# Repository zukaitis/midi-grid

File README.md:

# midi-grid
DIY RGB MIDI grid controller

midi-grid is an open source MIDI controller, main part of which is 8x8 LED illuminated button grid.

Main features of the device:
- 8x8 RGB LED illuminated button matrix
- 17 additional MIDI control buttons, most of them paired with RGB LED indicator
- 1 internal menu button
- 2 rotary encoders, acting as MIDI controls
- Monochrome LCD display with adjustable backlight
- Physical MIDI input and output ports

Currently device is developed to work with [Ableton Live](https://www.ableton.com/en/live/),
specifically with modified [Launchpad95](http://motscousus.com/stuff/2011-07_Novation_Launchpad_Ableton_Live_Scripts/)
MIDI remote script - [Launchpad95g](https://github.com/zukaitis/Launchpad95g). Additional functionality, like stand-alone modes,
or compatibility with other DAWs may be implemented later.

More thorough information, regarding design and implementation, is available in [wiki of this project](https://github.com/zukaitis/midi-grid/wiki).

**This repository uses submodules -** [here's info how to fully clone it](https://stackoverflow.com/questions/3796927/how-to-git-clone-including-submodules)

## Thanks to
- [@mimuz](https://github.com/mimuz) - for sharing [STM32 USB MIDI library](https://github.com/mimuz/mimuz-tuch)
- [@pidcodes](https://github.com/pidcodes) - for providing USB VID/PID pair for this application
- [@hdavid](https://github.com/hdavid) - for making an amazing Ableton Live extension - [Launchpad95](https://github.com/hdavid/Launchpad95)
- [@michaelbecker](https://github.com/michaelbecker) - for making [FreeRTOS C++ wrappers](https://michaelbecker.github.io/freertos-addons)

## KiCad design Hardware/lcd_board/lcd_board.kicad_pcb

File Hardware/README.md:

# Bill of Materials

| Reference | Quantity | Part number | Description | Catalog link
| --- | --- | --- | --- | ---
| A1 | 1 | Nokia 5110 LCD | LCD module, ILI9341 controller, TFT LCD Display, 9-pin breakout PCB, SPI interface, 5V/3.3V | https://www.ebay.com/itm/84-48-LCD-Module-White-Backlight-Adapter-PCB-for-Nokia-5110-Arduino/400488314619
| C3, C2, C1, C6, C7, C8, C9, C11, C13, C17 | 10 |  | Capacitor MLCC, 100nF +/-10%, 6.3V, 0603, X5R | 
| C12, C10, C4, C5 | 4 |  | Capacitor MLCC, 2.2uF +/-10%, 6.3V, 0603, X5R | 
| C14, C15 | 2 |  | Capacitor MLCC, 27pF +/-10%, 6.3V, 0603, C0G | 
| C16, C18, C19, C21, C20 | 5 |  | Capacitor MLCC, 10uF +/-10%, 6.3V, 1206, X5R | 
| D1, D3, D5, D7, D9, D11, D13, D15, D17, D19, D21, D23, D25, D27, D29, D31, D33, D35, D37, D39, D41, D43, D45, D47, D49, D51, D53, D55, D57, D59, D61, D63, D65, D67, D69, D71, D73, D75, D77, D79, D81, D83, D85, D87, D89, D91, D93, D95, D97, D99, D101, D103, D105, D107, D109, D111, D113, D115, D117, D119, D121, D123, D125, D127, D129, D132, D136, D140, D142, D148, D150, D156, D134, D144, D152, D146, D154 | 77 |  | RGB LED, TH, d=5mm, p=1.27mm, common anode, diffused, pinout: RAGB | https://www.ebay.com/itm/100pcs-x-5mm-RGB-LED-Common-Cathode-Tri-Color-Emitting-Diodes-Diffused/291498456335
| D2, D4, D6, D8, D10, D12, D14, D16, D18, D20, D22, D24, D26, D28, D30, D32, D34, D36, D38, D40, D42, D44, D46, D48, D50, D52, D54, D56, D58, D60, D62, D64, D66, D68, D70, D72, D74, D76, D78, D80, D82, D84, D86, D88, D90, D92, D94, D96, D98, D100, D102, D104, D106, D108, D110, D112, D114, D116, D118, D120, D122, D124, D126, D128, D130, D133, D137, D141, D143, D149, D151, D157, D131, D135, D138, D139, D145, D153, D147, D155, D158 | 81 | LL4148-GS08 | 100V 0.3A standard switching diode, MiniMELF | https://www.tme.eu/en/details/ll4148-gs08/smd-universal-diodes/vishay/
| F1 | 1 | 1206L050YR | Polyfuse, 6V, 500mA, 1206 | https://eu.mouser.com/productdetail/?qs=PWhpLWeW8wckT8hV5jLiAA%3D%3D
| J1 | 1 | 105017-0001 | Connector, Micro USB | https://www.lemona.lt/?page=item&i_id=216110
| J2, J3 | 2 | FC68133 | 3-pin audio jack receptable (stereo/TRS connector) with 2 switching contacts | http://lt.farnell.com/cliff-electronic-components/fc68133/stereo-jack-3-5mm-5pos-pcb/dp/2518190
| J4 | 1 | 22-27-2041 | Generic connector, single row, 01x04 | 
| Q2, Q1, Q4, Q3, Q6, Q5, Q8, Q7, Q10, Q9, Q12, Q11, Q14, Q13, Q16, Q15, Q18, Q17, Q20, Q19 | 20 | BSH205G2 | MOSFET, P Channel, -2 A, -20 V, SOT-23 | http://uk.farnell.com/nexperia/bsh205g2/mosfet-p-ch-20v-2a-to236ab/dp/2498570
| Q28, Q27, Q26, Q25, Q32, Q31, Q30, Q29, Q24, Q23, Q22, Q21, Q33, Q34 | 14 | NX7002AK | MOSFET, N-Channel, 190 mA, 60 V, SOT-23 | http://uk.farnell.com/nexperia/nx7002ak/mosfet-single-n-ch-60v-0-19a-sot23/dp/2191746
| R21, R22, R23, R24, R64 | 5 |  | Resistor, 1K +/-5%, 0603 | 
| R28, R27, R26, R25 | 4 |  | Resistor, 249R +/-1%, 1206 | 
| R36, R35, R34, R33 | 4 |  | Resistor, 294R +/-1%, 1206 | 
| R44, R43, R42, R41 | 4 |  | Resistor, 51R +/-1%, 1206 | 
| R40, R39, R38, R37, R48, R47, R46, R45, R32, R31, R30, R29, R1, R2, R3, R4, R5, R6, R7, R8, R9, R10, R11, R12, R13, R14, R15, R16, R17, R18, R19, R20, R52, R51, R50, R49, R53, R54, R55, R59, R56, R63 | 42 |  | Resistor, 10K +/-5% 0603 | 
| R57, R58, R61, R60, R62 | 5 |  | Resistor, 220R +/-5%, 0603 | 
| R65 | 1 |  | Resistor, 1.6K +/-5%, 0603 | 
| SW1, SW2, SW3, SW4 | 4 |  | 4 x 4 silicone push button matrix, button size: 15mm x 15mm, matrix size 100mm x 100mm | http://www.better-silicone.com/Translucent-Silicone-Rubber-Button-Pad-4x4-Keyboard-pd847135.html
| SW5, SW6, SW7, SW8, SW9, SW10, SW11, SW12, SW13, SW14, SW15, SW16, SW17, SW18, SW19, SW20, SW23, SW24 | 18 |  | Tactile switch with stem for cap, 12mm x 12mm, h=7.3mm | https://www.ebay.com/itm/25PCS-12x12x7-3mm-Tact-Tactile-Push-Button-Momentary-SMD-PCB-Switch-with-Cap/382202288162
|  | 17 |  | Button cap, round, d=12mm, black | 
|  | 1 |  | Button cap, round, d=12mm, red | 
| SW21, SW22 | 2 |  | Tactile switch, 6mm x 6mm, h=4.3mm | 
| SW25, SW26 | 2 | EC12E24204A9 | Rotary encoder, incremental, 24 pulses/revolution | 
| U1 | 1 | STM32F413RHT6 | Microcontroller, ARM Cortex-M4, LQFP64, Flash: 1536KB Ram: 320KB,100MHz Voltage: 1.7..3.6V IO-pins: 50 | 
| U4, U3, U2 | 3 | SN74HC138PW | Decoder 3 to 8 (active low outputs), TSSOP-16 | http://uk.farnell.com/texas-instruments/sn74hc138pw/ic-decoder-demux-smd/dp/9591095
| U5 | 1 | USBUF02W6 | 2-line EMI filter and ESD protection with R pull-up, for USB interfaces, SOT-363 | http://uk.farnell.com/stmicroelectronics/usbuf02w6/filter-low-pass-1ghz-sot-323-6/dp/2341659
| U6 | 1 | VO617A | Optocoupler, SO-4 | https://eu.mouser.com/ProductDetail/Vishay-Semiconductors/VO617A-8X017T?qs=%2fha2pyFaduga7JDI9Y4HlZSPCPCm8mReb3LRegGLigzOqtsvsZdCeQ%3d%3d
| U7 | 1 | LD1117STR | 800mA Low-Dropout Linear Regulator, adjustable output, SOT-223 | http://uk.farnell.com/stmicroelectronics/ld1117str/ic-v-reg-adj-1-25-15v-smd-1117/dp/1202824
| Y1 | 1 | ABM3B-8.000MHZ-B2-T | Crystal 8.0MHz 18pf 20ppm -20C +70C | https://eu.mouser.com/ProductDetail/?qs=NE97hfUNX0Ef9OqIOqO2cA%3D%3D
|  | 71 |  | Standoff, M2 * 5mm | https://www.ebay.com/itm/KNURLED-BRASS-SPACER-FEMALE-FEMALE-SCREW-PC-MOTHERBOARD-STANDOFF-M2-X-3MM-25MM-/122039617381
|  | 64 |  | Phillips screw, round head, M2 * 6mm | https://www.ebay.com/itm/M2-A2-304-Stainless-Steel-Phillips-Round-Head-Pan-Head-Screws-Bolts-M2-3-M2-60-/122691038427
|  | 23 |  | Phillips screw, flat head, M2 * 5mm | https://www.ebay.com/itm/M2-A2-304-Stainless-Steel-Phillips-Flat-Head-Screws-Bolts-M2-3mm-M2-60mm-/122689688965

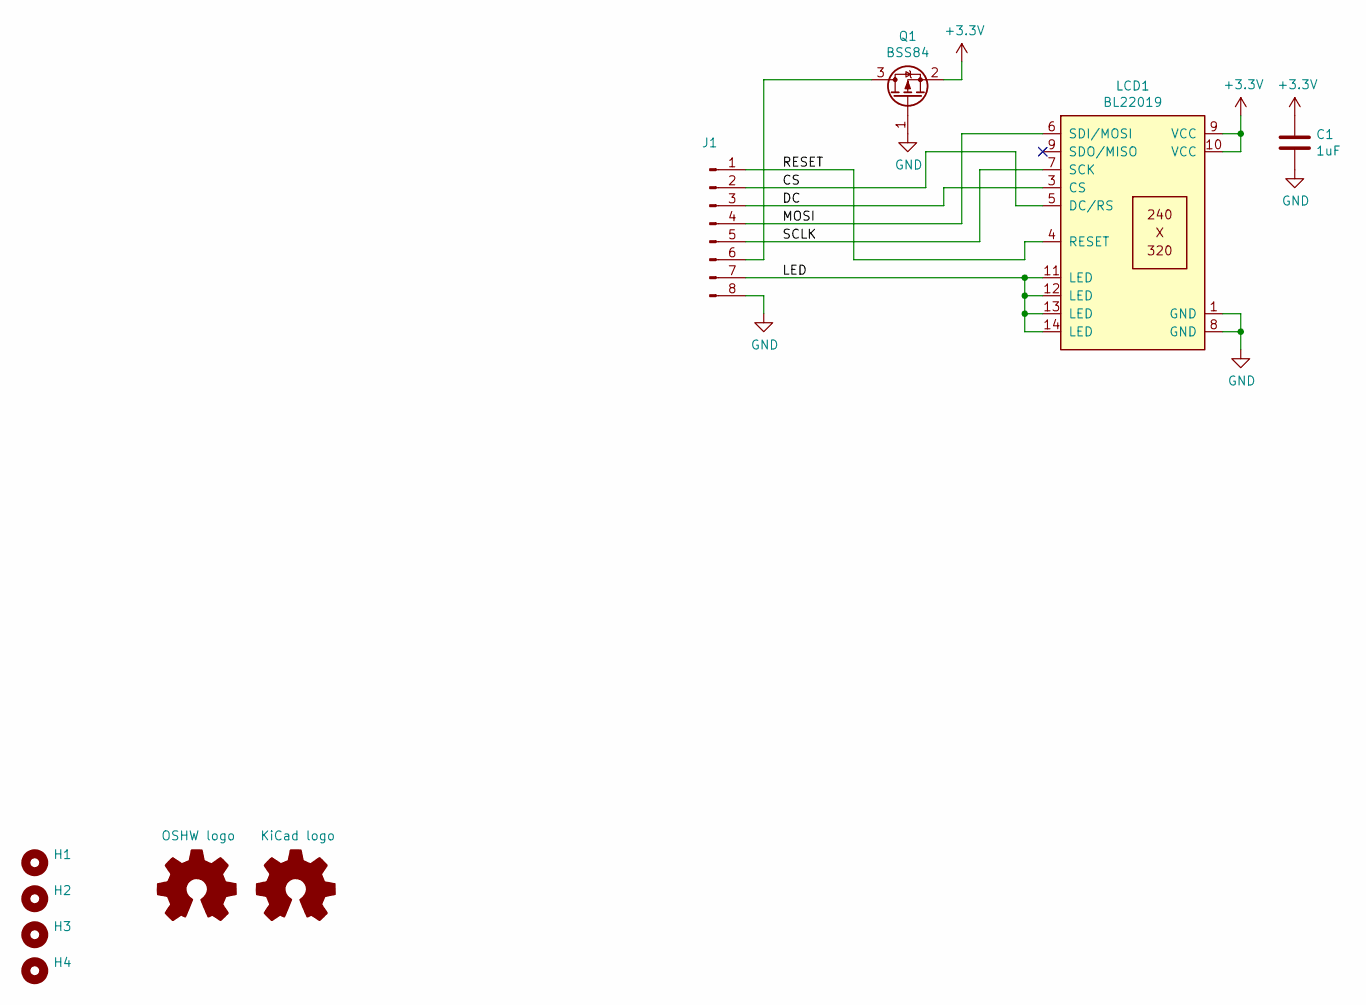
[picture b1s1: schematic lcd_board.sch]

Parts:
C1: 1uF; C_0805_2012Metric
H1, H2, H3, H4: MountingHole; MountingHole_2.2mm_M2
J1: Conn_01x08_Male; PinHeader_1x08_P2.54mm_Vertical_SMD_Pin1Left
LCD1: BL22019
LOGO1: OSHW logo; OSHW-Logo_11.4x12mm_Copper
LOGO2: KiCad logo; KiCad-Logo2_6mm_Copper
Q1: BSS84; SOT-23

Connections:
+3V3: C1.1, LCD1.9 (SDO/MISO), LCD1.10 (VCC), Q1.2 (S)
/CS: J1.2, LCD1.5 (DC/RS)
/DC: J1.3, LCD1.3 (CS)
/LED: J1.7, LCD1.11 (LED), LCD1.12 (LED), LCD1.13 (LED), LCD1.14 (LED)
/MOSI: J1.4, LCD1.6 (SDI/MOSI)
/RESET: J1.1, LCD1.4 (RESET)
/SCLK: J1.5, LCD1.7 (SCK)
GND: C1.2, J1.8, LCD1.1 (GND), LCD1.8 (GND), Q1.1 (G)
unnamed: J1.6, Q1.3 (D)

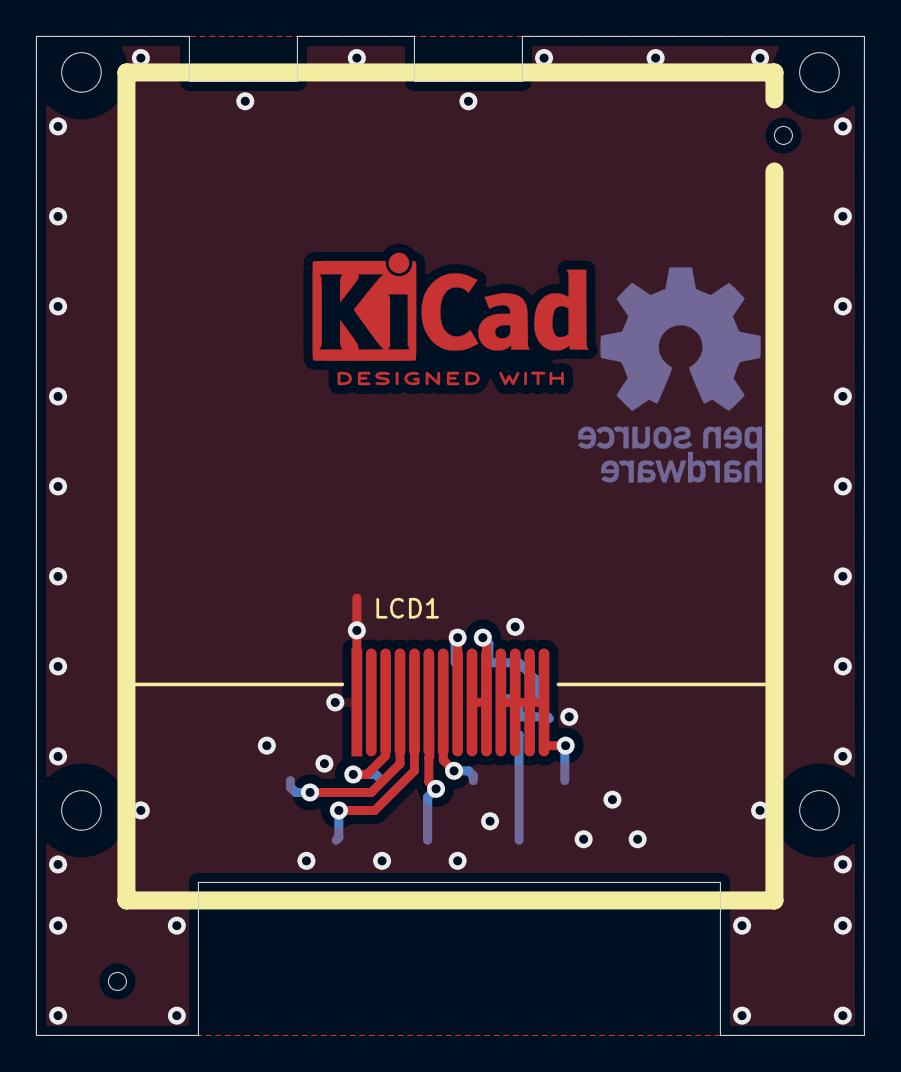
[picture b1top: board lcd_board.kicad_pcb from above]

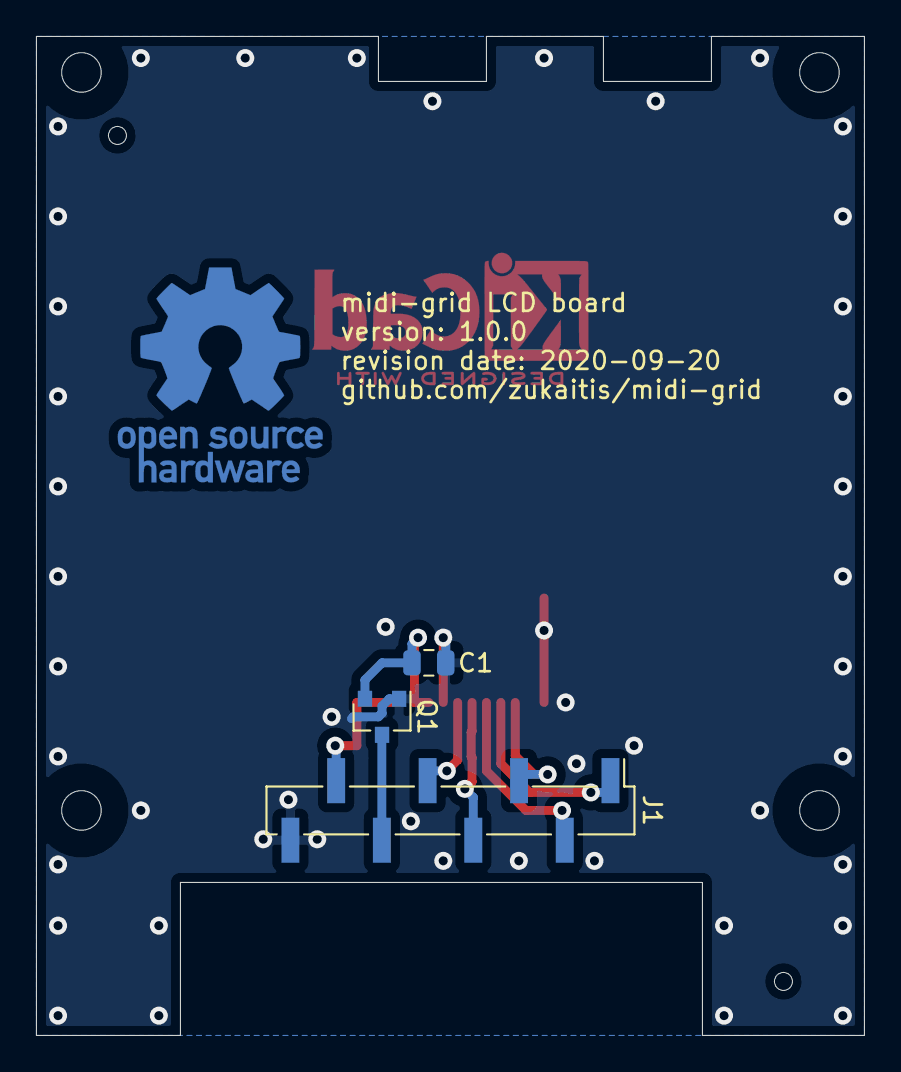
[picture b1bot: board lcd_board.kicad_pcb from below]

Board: 2 copper layers, 46.0 x 55.5 mm, 10 parts (4 on the bottom side), 9 nets.

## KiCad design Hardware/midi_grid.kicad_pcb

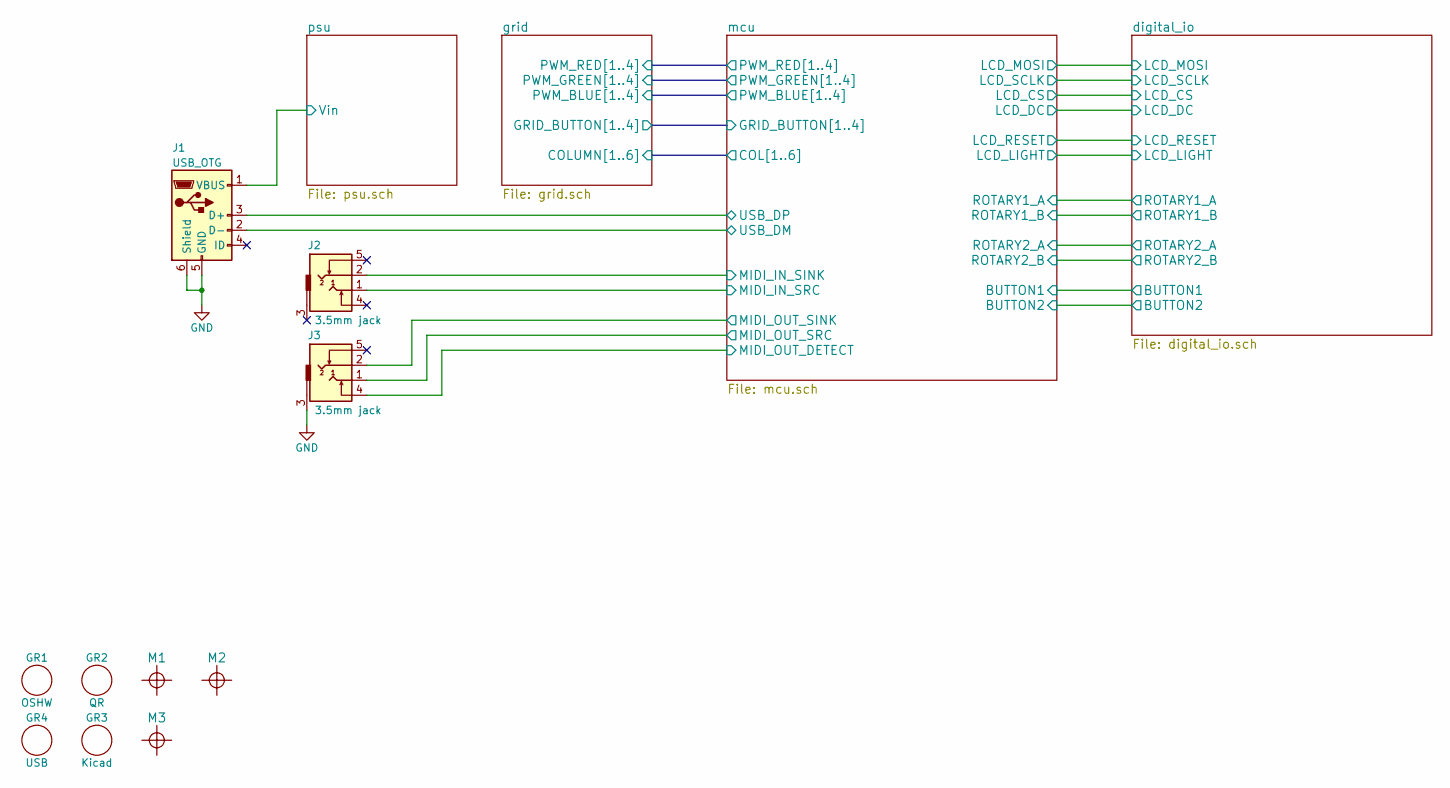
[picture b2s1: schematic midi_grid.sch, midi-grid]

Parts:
GR1: OSHW; Logo_OSHW
GR2: QR; qr_url
GR3: Kicad; Symbol_KiCAD-Logo_CopperAndSilkScreenTop
GR4: USB; usb_logo_6x3mm
J1: USB_OTG; USB_Micro-B_Molex-105017-0001
J2, J3: 3.5mm jack; 3.5mm-jack
M1, M2, M3: Mounting_hole; MountingHole_2.2mm_M2

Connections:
/mcu/MIDI_IN_SINK: J2.2; also elsewhere on the board
/mcu/MIDI_IN_SRC: J2.1; also elsewhere on the board
/mcu/MIDI_OUT_DETECT: J3.4; also elsewhere on the board
/mcu/MIDI_OUT_SINK: J3.2; also elsewhere on the board
/mcu/MIDI_OUT_SRC: J3.1; also elsewhere on the board
/mcu/USB_DM: J1.2 (D-); also elsewhere on the board
/mcu/USB_DP: J1.3 (D+); also elsewhere on the board
/psu/Vin: J1.1 (VBUS); also elsewhere on the board
GND: J1.5 (GND), J1.6 (Shield), J3.3; also elsewhere on the board

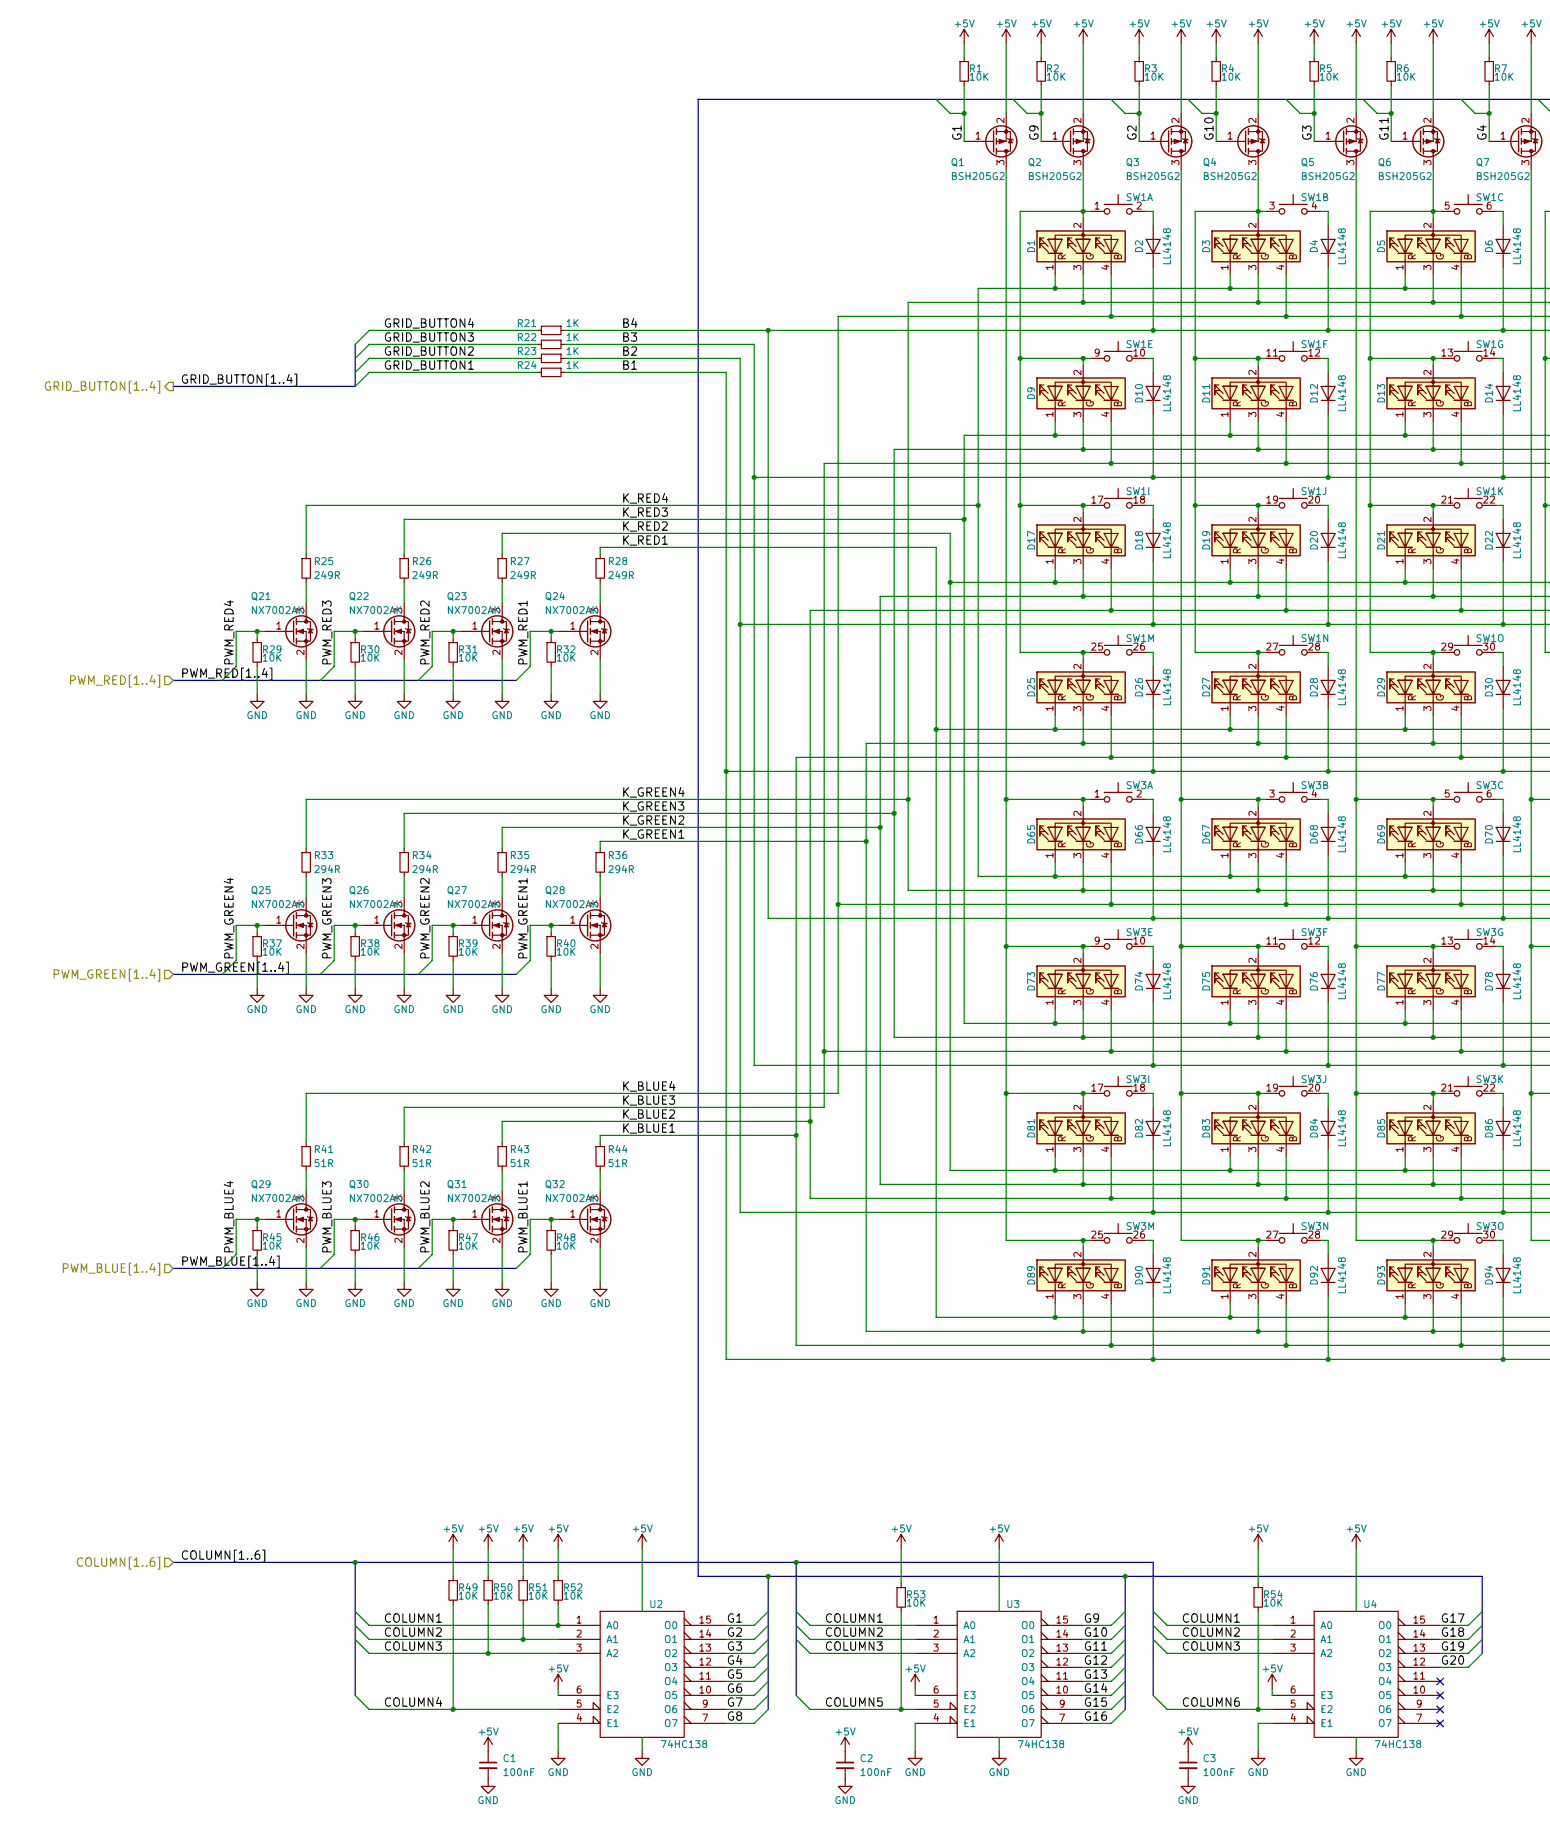
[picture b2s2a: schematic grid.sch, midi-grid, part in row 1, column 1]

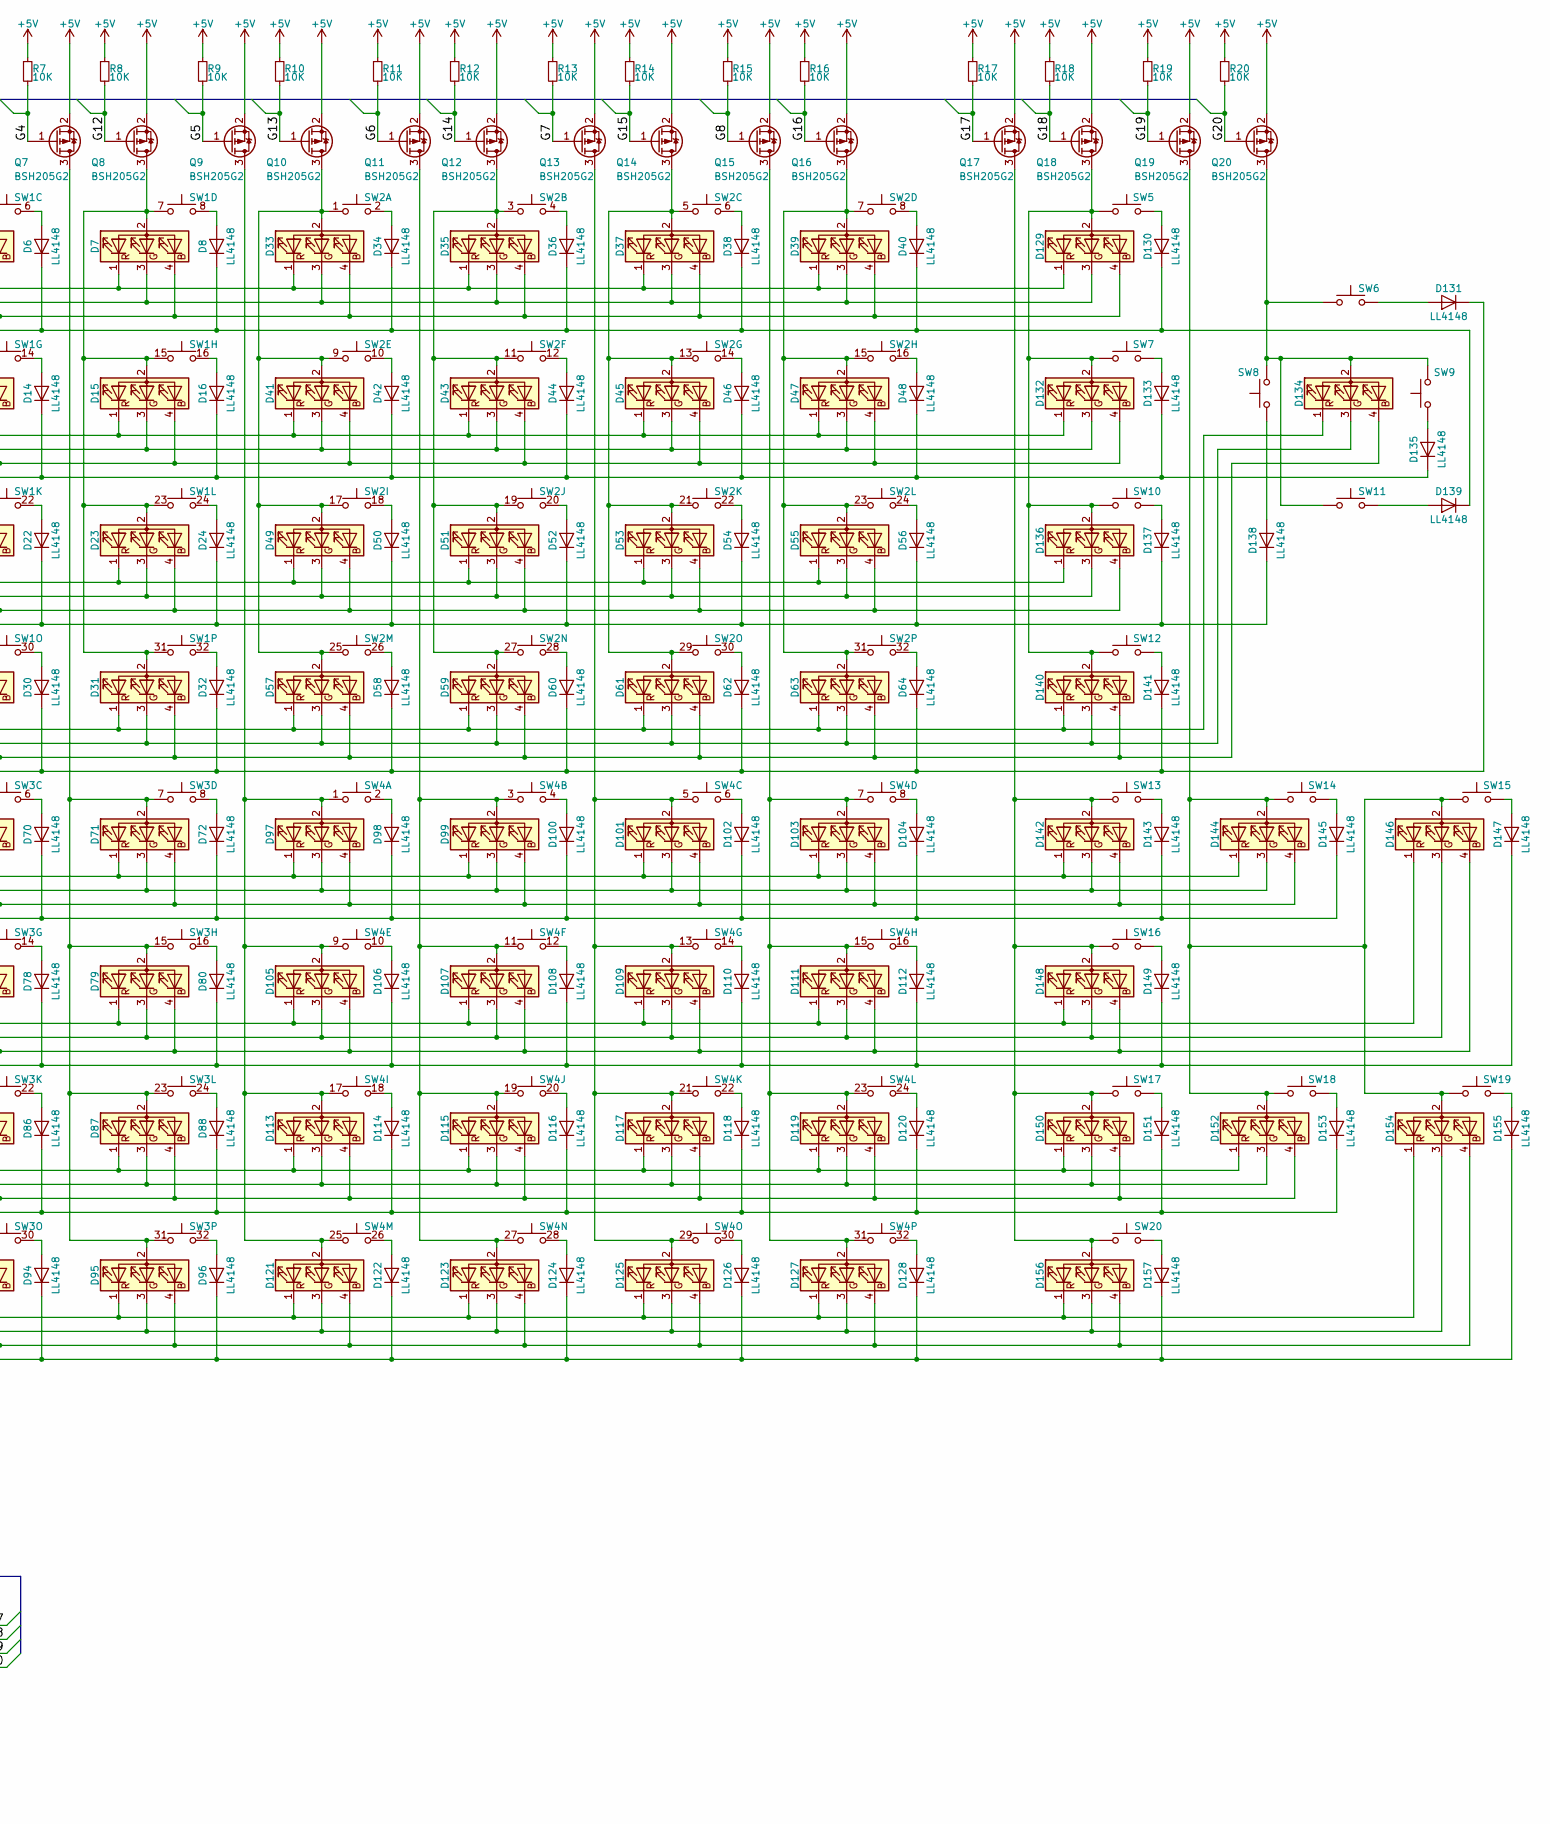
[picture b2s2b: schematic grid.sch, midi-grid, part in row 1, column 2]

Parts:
C1, C2, C3: 100nF; C_0603
D1, D3, D5, D7, D9, D11, D13, D15, D17, D19, D21, D23, D25, D27, D29, D31, D33, D35, D37, D39, D41, D43, D45, D47, D49, D51, D53, D55, D57, D59, D61, D63, D65, D67, D69, D71, D73, D75, D77, D79, D81, D83, D85, D87, D89, D91, D93, D95, D97, D99, D101, D103, D105, D107, D109, D111, D113, D115, D117, D119, D121, D123, D125, D127: LED_RAGB; LED_D5.0mm-4
D2, D4, D6, D8, D10, D12, D14, D16, D18, D20, D22, D24, D26, D28, D30, D32, D34, D36, D38, D40, D42, D44, D46, D48, D50, D52, D54, D56, D58, D60, D62, D64, D66, D68, D70, D72, D74, D76, D78, D80, D82, D84, D86, D88, D90, D92, D94, D96, D98, D100, D102, D104, D106, D108, D110, D112, D114, D116, D118, D120, D122, D124, D126, D128, D130, D131, D133, D135, D137, D138, D139, D141, D143, D145, D147, D149, D151, D153, D155, D157: LL4148; D_MiniMELF
D129, D132, D134, D136, D140, D142, D144, D146, D148, D150, D152, D154, D156: LED_RAGB; LED_D5.0mm-4-4mm_standoff
Q1, Q2, Q3, Q4, Q5, Q6, Q7, Q8, Q9, Q10, Q11, Q12, Q13, Q14, Q15, Q16, Q17, Q18, Q19, Q20: BSH205G2; SOT-23
Q21, Q22, Q23, Q24, Q25, Q26, Q27, Q28, Q29, Q30, Q31, Q32: NX7002AK; SOT-23
R1, R2, R3, R4, R5, R6, R7, R8, R9, R10, R11, R12, R13, R14, R15, R16, R17, R18, R19, R20, R29, R30, R31, R32, R37, R38, R39, R40, R45, R46, R47, R48, R49, R50, R51, R52, R53, R54: 10K; R_0603
R21, R22, R23, R24: 1K; R_0603
R25, R26, R27, R28: 249R; R_1206
R33, R34, R35, R36: 294R; R_1206
R41, R42, R43, R44: 51R; R_1206
SW1, SW2, SW3, SW4: Button_matrix_4x4; 4x4_silicone_button_matrix
SW5, SW7, SW10, SW12, SW13, SW14, SW15, SW16, SW17, SW18, SW19, SW20: SW_Push; Tactile_switch_12x12
SW6, SW8, SW9, SW11: SW_Push; Tactile_switch_12x12_no_holes
U2, U3, U4: 74HC138; TSSOP-16_4.4x5mm_Pitch0.65mm

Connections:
+5V: C1.1, C2.1, C3.1, Q1.2 (S), Q2.2 (S), Q3.2 (S), Q4.2 (S), Q5.2 (S), Q6.2 (S), Q7.2 (S), Q8.2 (S), Q9.2 (S), Q10.2 (S), Q11.2 (S), Q12.2 (S), Q13.2 (S), Q14.2 (S), Q15.2 (S), Q16.2 (S), Q17.2 (S), Q18.2 (S), Q19.2 (S), Q20.2 (S), R1.1, R2.1, R3.1, R4.1, R5.1, R6.1, R7.1, R8.1, R9.1, R10.1, R11.1, R12.1, R13.1, R14.1, R15.1, R16.1, R17.1, R18.1, R19.1, R20.1, R49.1, R50.1, R51.1, R52.1, R53.1, R54.1, U2.6 (E3), U2.16 (VCC), U3.6 (E3), U3.16 (VCC), U4.6 (E3), U4.16 (VCC); also elsewhere on the board
/grid/B1: D26.1 (K), D28.1 (K), D30.1 (K), D32.1 (K), D58.1 (K), D60.1 (K), D62.1 (K), D64.1 (K), D90.1 (K), D92.1 (K), D94.1 (K), D96.1 (K), D122.1 (K), D124.1 (K), D126.1 (K), D128.1 (K), D131.1 (K), D141.1 (K), D155.1 (K), D157.1 (K), R24.1
/grid/B2: D18.1 (K), D20.1 (K), D22.1 (K), D24.1 (K), D50.1 (K), D52.1 (K), D54.1 (K), D56.1 (K), D82.1 (K), D84.1 (K), D86.1 (K), D88.1 (K), D114.1 (K), D116.1 (K), D118.1 (K), D120.1 (K), D137.1 (K), D138.1 (K), D151.1 (K), D153.1 (K), R23.1
/grid/B3: D10.1 (K), D12.1 (K), D14.1 (K), D16.1 (K), D42.1 (K), D44.1 (K), D46.1 (K), D48.1 (K), D74.1 (K), D76.1 (K), D78.1 (K), D80.1 (K), D106.1 (K), D108.1 (K), D110.1 (K), D112.1 (K), D133.1 (K), D135.1 (K), D147.1 (K), D149.1 (K), R22.1
/grid/B4: D2.1 (K), D4.1 (K), D6.1 (K), D8.1 (K), D34.1 (K), D36.1 (K), D38.1 (K), D40.1 (K), D66.1 (K), D68.1 (K), D70.1 (K), D72.1 (K), D98.1 (K), D100.1 (K), D102.1 (K), D104.1 (K), D130.1 (K), D139.1 (K), D143.1 (K), D145.1 (K), R21.1
/grid/G1: Q1.1 (G), R1.2, U2.15 (O0)
/grid/G2: Q3.1 (G), R3.2, U2.14 (O1)
/grid/G3: Q5.1 (G), R5.2, U2.13 (O2)
/grid/G4: Q7.1 (G), R7.2, U2.12 (O3)
/grid/G5: Q9.1 (G), R9.2, U2.11 (O4)
/grid/G6: Q11.1 (G), R11.2, U2.10 (O5)
/grid/G7: Q13.1 (G), R13.2, U2.9 (O6)
/grid/G8: Q15.1 (G), R15.2, U2.7 (O7)
/grid/G9: Q2.1 (G), R2.2, U3.15 (O0)
/grid/G10: Q4.1 (G), R4.2, U3.14 (O1)
/grid/G11: Q6.1 (G), R6.2, U3.13 (O2)
/grid/G12: Q8.1 (G), R8.2, U3.12 (O3)
/grid/G13: Q10.1 (G), R10.2, U3.11 (O4)
/grid/G14: Q12.1 (G), R12.2, U3.10 (O5)
/grid/G15: Q14.1 (G), R14.2, U3.9 (O6)
/grid/G16: Q16.1 (G), R16.2, U3.7 (O7)
/grid/G17: Q17.1 (G), R17.2, U4.15 (O0)
/grid/G18: Q18.1 (G), R18.2, U4.14 (O1)
/grid/G19: Q19.1 (G), R19.2, U4.13 (O2)
/grid/G20: Q20.1 (G), R20.2, U4.12 (O3)
/grid/GRID_BUTTON1: R24.2; also elsewhere on the board
/grid/GRID_BUTTON2: R23.2; also elsewhere on the board
/grid/GRID_BUTTON3: R22.2; also elsewhere on the board
/grid/GRID_BUTTON4: R21.2; also elsewhere on the board
/grid/K_BLUE1: D25.4 (BK), D27.4 (BK), D29.4 (BK), D31.4 (BK), D57.4 (BK), D59.4 (BK), D61.4 (BK), D63.4 (BK), D89.4 (BK), D91.4 (BK), D93.4 (BK), D95.4 (BK), D121.4 (BK), D123.4 (BK), D125.4 (BK), D127.4 (BK), D134.4 (BK), D140.4 (BK), D154.4 (BK), D156.4 (BK), R44.1
/grid/K_BLUE2: D17.4 (BK), D19.4 (BK), D21.4 (BK), D23.4 (BK), D49.4 (BK), D51.4 (BK), D53.4 (BK), D55.4 (BK), D81.4 (BK), D83.4 (BK), D85.4 (BK), D87.4 (BK), D113.4 (BK), D115.4 (BK), D117.4 (BK), D119.4 (BK), D136.4 (BK), D150.4 (BK), D152.4 (BK), R43.1
/grid/K_BLUE3: D9.4 (BK), D11.4 (BK), D13.4 (BK), D15.4 (BK), D41.4 (BK), D43.4 (BK), D45.4 (BK), D47.4 (BK), D73.4 (BK), D75.4 (BK), D77.4 (BK), D79.4 (BK), D105.4 (BK), D107.4 (BK), D109.4 (BK), D111.4 (BK), D132.4 (BK), D146.4 (BK), D148.4 (BK), R42.1
/grid/K_BLUE4: D1.4 (BK), D3.4 (BK), D5.4 (BK), D7.4 (BK), D33.4 (BK), D35.4 (BK), D37.4 (BK), D39.4 (BK), D65.4 (BK), D67.4 (BK), D69.4 (BK), D71.4 (BK), D97.4 (BK), D99.4 (BK), D101.4 (BK), D103.4 (BK), D129.4 (BK), D142.4 (BK), D144.4 (BK), R41.1
/grid/K_GREEN1: D25.3 (GK), D27.3 (GK), D29.3 (GK), D31.3 (GK), D57.3 (GK), D59.3 (GK), D61.3 (GK), D63.3 (GK), D89.3 (GK), D91.3 (GK), D93.3 (GK), D95.3 (GK), D121.3 (GK), D123.3 (GK), D125.3 (GK), D127.3 (GK), D134.3 (GK), D140.3 (GK), D154.3 (GK), D156.3 (GK), R36.1
/grid/K_GREEN2: D17.3 (GK), D19.3 (GK), D21.3 (GK), D23.3 (GK), D49.3 (GK), D51.3 (GK), D53.3 (GK), D55.3 (GK), D81.3 (GK), D83.3 (GK), D85.3 (GK), D87.3 (GK), D113.3 (GK), D115.3 (GK), D117.3 (GK), D119.3 (GK), D136.3 (GK), D150.3 (GK), D152.3 (GK), R35.1
/grid/K_GREEN3: D9.3 (GK), D11.3 (GK), D13.3 (GK), D15.3 (GK), D41.3 (GK), D43.3 (GK), D45.3 (GK), D47.3 (GK), D73.3 (GK), D75.3 (GK), D77.3 (GK), D79.3 (GK), D105.3 (GK), D107.3 (GK), D109.3 (GK), D111.3 (GK), D132.3 (GK), D146.3 (GK), D148.3 (GK), R34.1
/grid/K_GREEN4: D1.3 (GK), D3.3 (GK), D5.3 (GK), D7.3 (GK), D33.3 (GK), D35.3 (GK), D37.3 (GK), D39.3 (GK), D65.3 (GK), D67.3 (GK), D69.3 (GK), D71.3 (GK), D97.3 (GK), D99.3 (GK), D101.3 (GK), D103.3 (GK), D129.3 (GK), D142.3 (GK), D144.3 (GK), R33.1
/grid/K_RED1: D25.1 (RK), D27.1 (RK), D29.1 (RK), D31.1 (RK), D57.1 (RK), D59.1 (RK), D61.1 (RK), D63.1 (RK), D89.1 (RK), D91.1 (RK), D93.1 (RK), D95.1 (RK), D121.1 (RK), D123.1 (RK), D125.1 (RK), D127.1 (RK), D134.1 (RK), D140.1 (RK), D154.1 (RK), D156.1 (RK), R28.1
/grid/K_RED2: D17.1 (RK), D19.1 (RK), D21.1 (RK), D23.1 (RK), D49.1 (RK), D51.1 (RK), D53.1 (RK), D55.1 (RK), D81.1 (RK), D83.1 (RK), D85.1 (RK), D87.1 (RK), D113.1 (RK), D115.1 (RK), D117.1 (RK), D119.1 (RK), D136.1 (RK), D150.1 (RK), D152.1 (RK), R27.1
/grid/K_RED3: D9.1 (RK), D11.1 (RK), D13.1 (RK), D15.1 (RK), D41.1 (RK), D43.1 (RK), D45.1 (RK), D47.1 (RK), D73.1 (RK), D75.1 (RK), D77.1 (RK), D79.1 (RK), D105.1 (RK), D107.1 (RK), D109.1 (RK), D111.1 (RK), D132.1 (RK), D146.1 (RK), D148.1 (RK), R26.1
/grid/K_RED4: D1.1 (RK), D3.1 (RK), D5.1 (RK), D7.1 (RK), D33.1 (RK), D35.1 (RK), D37.1 (RK), D39.1 (RK), D65.1 (RK), D67.1 (RK), D69.1 (RK), D71.1 (RK), D97.1 (RK), D99.1 (RK), D101.1 (RK), D103.1 (RK), D129.1 (RK), D142.1 (RK), D144.1 (RK), R25.1
/grid/PWM_BLUE1: Q32.1 (G), R48.1; also elsewhere on the board
/grid/PWM_BLUE2: Q31.1 (G), R47.1; also elsewhere on the board
/grid/PWM_BLUE3: Q30.1 (G), R46.1; also elsewhere on the board
/grid/PWM_BLUE4: Q29.1 (G), R45.1; also elsewhere on the board
/grid/PWM_GREEN1: Q28.1 (G), R40.1; also elsewhere on the board
/grid/PWM_GREEN2: Q27.1 (G), R39.1; also elsewhere on the board
/grid/PWM_GREEN3: Q26.1 (G), R38.1; also elsewhere on the board
/grid/PWM_GREEN4: Q25.1 (G), R37.1; also elsewhere on the board
/grid/PWM_RED1: Q24.1 (G), R32.1; also elsewhere on the board
/grid/PWM_RED2: Q23.1 (G), R31.1; also elsewhere on the board
/grid/PWM_RED3: Q22.1 (G), R30.1; also elsewhere on the board
/grid/PWM_RED4: Q21.1 (G), R29.1; also elsewhere on the board
/mcu/COL1: R52.2, U2.1 (A0), U3.1 (A0), U4.1 (A0); also elsewhere on the board
/mcu/COL2: R51.2, U2.2 (A1), U3.2 (A1), U4.2 (A1); also elsewhere on the board
/mcu/COL3: R50.2, U2.3 (A2), U3.3 (A2), U4.3 (A2); also elsewhere on the board
/mcu/COL4: R49.2, U2.5 (E2); also elsewhere on the board
/mcu/COL5: R53.2, U3.5 (E2); also elsewhere on the board
/mcu/COL6: R54.2, U4.5 (E2); also elsewhere on the board
GND: C1.2, C2.2, C3.2, Q21.2 (S), Q22.2 (S), Q23.2 (S), Q24.2 (S), Q25.2 (S), Q26.2 (S), Q27.2 (S), Q28.2 (S), Q29.2 (S), Q30.2 (S), Q31.2 (S), Q32.2 (S), R29.2, R30.2, R31.2, R32.2, R37.2, R38.2, R39.2, R40.2, R45.2, R46.2, R47.2, R48.2, U2.4 (E1), U2.8 (GND), U3.4 (E1), U3.8 (GND), U4.4 (E1), U4.8 (GND); also elsewhere on the board
unnamed: D1.2 (A), D9.2 (A), D17.2 (A), D25.2 (A), Q2.3 (D), SW1.1, SW1.9, SW1.17, SW1.25
unnamed: D2.2 (A), SW1.2
unnamed: D4.2 (A), SW1.4
unnamed: D6.2 (A), SW1.6
unnamed: D8.2 (A), SW1.8
unnamed: D10.2 (A), SW1.10
unnamed: D3.2 (A), D11.2 (A), D19.2 (A), D27.2 (A), Q4.3 (D), SW1.3, SW1.11, SW1.19, SW1.27
unnamed: D12.2 (A), SW1.12
unnamed: D5.2 (A), D13.2 (A), D21.2 (A), D29.2 (A), Q6.3 (D), SW1.5, SW1.13, SW1.21, SW1.29
unnamed: D14.2 (A), SW1.14
unnamed: D7.2 (A), D15.2 (A), D23.2 (A), D31.2 (A), Q8.3 (D), SW1.7, SW1.15, SW1.23, SW1.31
unnamed: D16.2 (A), SW1.16
unnamed: D18.2 (A), SW1.18
unnamed: D20.2 (A), SW1.20
unnamed: D22.2 (A), SW1.22
unnamed: D24.2 (A), SW1.24
unnamed: D26.2 (A), SW1.26
unnamed: D28.2 (A), SW1.28
unnamed: D30.2 (A), SW1.30
unnamed: D32.2 (A), SW1.32
unnamed: D33.2 (A), D41.2 (A), D49.2 (A), D57.2 (A), Q10.3 (D), SW2.1, SW2.9, SW2.17, SW2.25
unnamed: D34.2 (A), SW2.2
unnamed: D35.2 (A), D43.2 (A), D51.2 (A), D59.2 (A), Q12.3 (D), SW2.3, SW2.11, SW2.19, SW2.27
unnamed: D36.2 (A), SW2.4
unnamed: D37.2 (A), D45.2 (A), D53.2 (A), D61.2 (A), Q14.3 (D), SW2.5, SW2.13, SW2.21, SW2.29
unnamed: D38.2 (A), SW2.6
unnamed: D39.2 (A), D47.2 (A), D55.2 (A), D63.2 (A), Q16.3 (D), SW2.7, SW2.15, SW2.23, SW2.31
unnamed: D40.2 (A), SW2.8
unnamed: D42.2 (A), SW2.10
unnamed: D44.2 (A), SW2.12
unnamed: D46.2 (A), SW2.14
unnamed: D48.2 (A), SW2.16
unnamed: D50.2 (A), SW2.18
unnamed: D52.2 (A), SW2.20
unnamed: D54.2 (A), SW2.22
unnamed: D56.2 (A), SW2.24
unnamed: D58.2 (A), SW2.26
unnamed: D60.2 (A), SW2.28
unnamed: D62.2 (A), SW2.30
unnamed: D64.2 (A), SW2.32
unnamed: D65.2 (A), D73.2 (A), D81.2 (A), D89.2 (A), Q1.3 (D), SW3.1, SW3.9, SW3.17, SW3.25
unnamed: D66.2 (A), SW3.2
unnamed: D67.2 (A), D75.2 (A), D83.2 (A), D91.2 (A), Q3.3 (D), SW3.3, SW3.11, SW3.19, SW3.27
unnamed: D68.2 (A), SW3.4
unnamed: D69.2 (A), D77.2 (A), D85.2 (A), D93.2 (A), Q5.3 (D), SW3.5, SW3.13, SW3.21, SW3.29
unnamed: D70.2 (A), SW3.6
unnamed: D71.2 (A), D79.2 (A), D87.2 (A), D95.2 (A), Q7.3 (D), SW3.7, SW3.15, SW3.23, SW3.31
unnamed: D72.2 (A), SW3.8
unnamed: D74.2 (A), SW3.10
unnamed: D76.2 (A), SW3.12
unnamed: D78.2 (A), SW3.14
unnamed: D80.2 (A), SW3.16
unnamed: D82.2 (A), SW3.18
unnamed: D84.2 (A), SW3.20
unnamed: D86.2 (A), SW3.22
unnamed: D88.2 (A), SW3.24
unnamed: D90.2 (A), SW3.26
unnamed: D92.2 (A), SW3.28
unnamed: D94.2 (A), SW3.30
unnamed: D96.2 (A), SW3.32
unnamed: D98.2 (A), SW4.2
unnamed: D100.2 (A), SW4.4
unnamed: D101.2 (A), D109.2 (A), D117.2 (A), D125.2 (A), Q13.3 (D), SW4.5, SW4.13, SW4.21, SW4.29
unnamed: D102.2 (A), SW4.6
unnamed: D103.2 (A), D111.2 (A), D119.2 (A), D127.2 (A), Q15.3 (D), SW4.7, SW4.15, SW4.23, SW4.31
unnamed: D104.2 (A), SW4.8
unnamed: D97.2 (A), D105.2 (A), D113.2 (A), D121.2 (A), Q9.3 (D), SW4.1, SW4.9, SW4.17, SW4.25
unnamed: D106.2 (A), SW4.10
unnamed: D99.2 (A), D107.2 (A), D115.2 (A), D123.2 (A), Q11.3 (D), SW4.3, SW4.11, SW4.19, SW4.27
unnamed: D108.2 (A), SW4.12
unnamed: D110.2 (A), SW4.14
unnamed: D112.2 (A), SW4.16
unnamed: D114.2 (A), SW4.18
unnamed: D116.2 (A), SW4.20
unnamed: D118.2 (A), SW4.22
unnamed: D120.2 (A), SW4.24
unnamed: D122.2 (A), SW4.26
unnamed: D124.2 (A), SW4.28
unnamed: D126.2 (A), SW4.30
unnamed: D128.2 (A), SW4.32
unnamed: D129.2 (A), D132.2 (A), D136.2 (A), D140.2 (A), Q18.3 (D), SW5.2, SW7.2, SW10.2, SW12.2
unnamed: D130.2 (A), SW5.1
unnamed: D131.2 (A), SW6.2
unnamed: D133.2 (A), SW7.1
unnamed: D134.2 (A), Q20.3 (D), SW6.1, SW8.2, SW9.1, SW11.1
unnamed: D135.2 (A), SW9.2
unnamed: D137.2 (A), SW10.1
unnamed: D138.2 (A), SW8.1
unnamed: D139.2 (A), SW11.2
unnamed: D141.2 (A), SW12.1
unnamed: D142.2 (A), D148.2 (A), D150.2 (A), D156.2 (A), Q17.3 (D), SW13.2, SW16.2, SW17.2, SW20.2
unnamed: D143.2 (A), SW13.1
unnamed: D144.2 (A), D146.2 (A), D152.2 (A), D154.2 (A), Q19.3 (D), SW14.2, SW15.2, SW18.2, SW19.2
unnamed: D145.2 (A), SW14.1
unnamed: D147.2 (A), SW15.1
unnamed: D149.2 (A), SW16.1
unnamed: D151.2 (A), SW17.1
unnamed: D153.2 (A), SW18.1
unnamed: D155.2 (A), SW19.1
unnamed: D157.2 (A), SW20.1
unnamed: Q21.3 (D), R25.2
unnamed: Q22.3 (D), R26.2
unnamed: Q23.3 (D), R27.2
unnamed: Q24.3 (D), R28.2
unnamed: Q25.3 (D), R33.2
unnamed: Q26.3 (D), R34.2
unnamed: Q27.3 (D), R35.2
unnamed: Q28.3 (D), R36.2
unnamed: Q29.3 (D), R41.2
unnamed: Q30.3 (D), R42.2
unnamed: Q31.3 (D), R43.2
unnamed: Q32.3 (D), R44.2
